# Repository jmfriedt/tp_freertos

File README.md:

# FreeRTOS on STM32 laboratory sessions

TP FreeRTOS on STM32F1VLDiscovery board or STM32F103 (update the LD script accordingly)

Assumes the Long Term Supported version of FreeRTOS as available at https://github.com/FreeRTOS/FreeRTOS-LTS 
(remember to ``git clone --recursive``), or the version found at https://www.freertos.org/a00104.html, is located at the same level than this set of examples: tune the Makefiles
accordingly for the header files and libraries to reach this directory. Former versions of FreeRTOSv9.0.0 or 
FreeRTOSv10.0.0 can be used as well: in that case tune the parameters of Makefile.v9 accordingly).

Compilation flags:
* ``-DSTM32F1`` or ``-DSTM32F4`` to select whether the board is fitted with and STM32F100/STM32F103 microcontroller
or with a STM32F407 (STM32F4Discovery)
* in case ``-DSTM32F1`` is selected, either select ``-DSTM32F10X_LD_VL`` for the STM32F100 ValueLine or the
``-DSTM32F10X_MD`` MediumDevice
* in case ``-DSTM32F10X_MD`` is selected, then add ``-Dsenseor`` for running on the hardware board (SENSeOR reader
fitted with the XE1203F radiomodem) without resetting the FTDI (keeping the GPIO connected to the FT232
reset pin as input). For running on Qemu, do not enable ``-Dsenseor``.
* the Texas Instruments Stellaris Cortex M4F core is supported and allows for simulating the execution
on the official qemu-system-arm emulator release: in that case, the linker script is ``stellaris.ld`` found in the ``ld`` directory.

Using ``libopencm3`` to provide system calls required by FreeRTOS running on the STM32 microcontroller (instead
of ST Microelectronics' libstm32) is described at http://www.jiggerjuice.info/electronics/projects/arm/freertos-stm32f103-port.html 
and was used in this set of demonstrations.

Tested with Andre Beckus' port of qemu to the stm32 (https://github.com/beckus/qemu_stm32): compile examples
for the STM32F103 (MD) device. Also tested with Renode (https://github.com/renode) emulating the STM32F103:

The Renode model has been updated to display GPIO/LED output state. Here also the very verbose gpioPortC status is displayed,
which can be removed by commenting (prefix with ``:``) the ``sysbus LogPeripheralAccess sysbus.gpioPortC`` line
in 1basic/stm32f103.resc

This set of laboratory sessions was developed independently but happens to closely match the topics of [Beginning STM32: Developing with FreeRTOS, libopencm3 and GCC](https://www.amazon.fr/Beginning-STM32-Developing-FreeRTOS-libopencm3/dp/1484236238) which might provide additional references to my own supporting material found at http://jmfriedt.free.fr under the Master1 section/embedded electronics/2nd semester. The
[github](https://github.com/ve3wwg/stm32f103c8t6) might provide complementary resources.

## References (in French)

* Q. Macé, J.-M Friedt, *FreeRTOS : application à la réalisation d'un analyseur de réseau 
numérique sur STM32*, <a href="http://jmfriedt.free.fr/lm_freertos.pdf">GNU/Linux Magazine France 
207</a> (Sept. 2017)
* J.-M Friedt, *Intercorrélation par transformée de Fourier rapide sur microcontroleur sous 
FreeRTOS, et les pointeurs de pointeurs*, <a href="http://jmfriedt.free.fr/lm_fft.pdf">Hackable 43 
</a>pp.4-- (Jul.-Aug. 2022)
* J.-M Friedt, *FreeRTOS dans 2,5 KB de RAM sur Atmega32U4*, <a href="http://jmfriedt.free.fr/hackable_atmega32u4.pdf">Hackable 48</a> (May/June 2023)

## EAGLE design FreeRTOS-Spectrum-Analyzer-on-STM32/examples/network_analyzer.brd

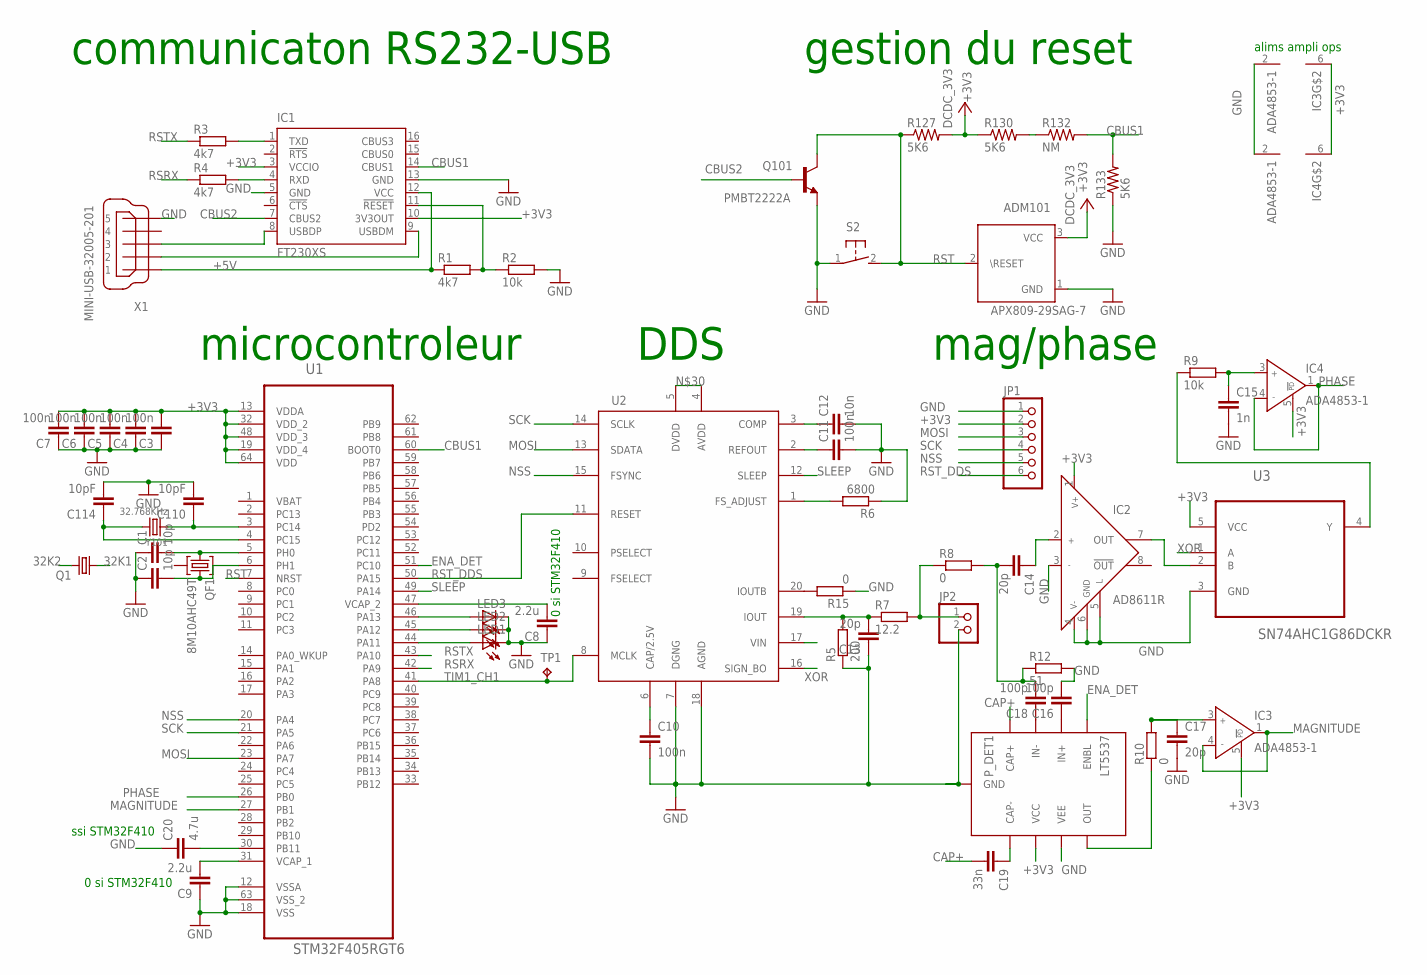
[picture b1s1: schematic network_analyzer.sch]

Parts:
ADM101: APX809-29SAG-7; CIS_SOT23_01
C1, C2: 10p; C0603
C3, C4, C5, C6, C7, C10, C11: 100n; C0603
C8, C9: 2.2u; C0402
C12: 10n; C0603
C13, C14, C17: 20p; C0603
C15: 1n; C0603
C16, C18: 100p; C0603
C19: 33n; C0603
C20: 4.7u; C0603
C110, C114: 10pF; C0402
IC1: FT230XS; SSOP16
IC2: AD8611R; SO8
IC3, IC4: ADA4853-1; SC70-6
JP1: PINHD-1X6; 1X06
JP2: PINHD-1X2; 1X02
LED1, LED2, LED3: LEDSML0603; SML0603
P_DET1: LT5537; 3X2MMDFN
Q1: CRYSTALTC26H; TC26H
Q101: PMBT2222A; Q-S_SOT23_01
QF1: 8M10AHC49T; HC49U
R1, R3, R4: 4k7; R0603
R2, R9: 10k; R0603
R5: 200; R0603
R6: 6800; R0603
R7: 12.2; 0207/10
R8, R10, R15: 0; R0603
R12: 51; R0603
R127, R130, R133: 5K6; R0402
R132: NM; R0402
S2: 31-XX; B3F-31XX
TP1: TPB1,27; B1,27
U1: STM32F405RGT6; QFP50P1200X1200X160-64N
U2: AD9834; TSSOP20
U3: SN74AHC1G86DCKR; SOT65P210X110-5N
X1: MINI-USB-32005-201; 32005-201
Y101: 32.768KHz; Y-S_3215_01

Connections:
32K1: C110.1, Q1.1, U1.3 (PC14), Y101.1
32K2: C114.1, Q1.2, U1.4 (PC15), Y101.2
+3V3: ADM101.3 (VCC), C3.2, C4.2, C5.2, C6.2, C7.2, IC1.3 (VCCIO), IC1.10 (3V3OUT), IC2.1 (V+), IC3.5 (!POWERDOWN), IC3.6 (V+), IC4.5 (!POWERDOWN), IC4.6 (V+), JP1.2, P_DET1.P$6 (VCC), R127.2, R130.1, U1.13 (VDDA), U1.19 (VDD_4), U1.32 (VDD_2), U1.48 (VDD_3), U1.64 (VDD), U3.5 (VCC)
+5V: IC1.12 (VCC), R1.1, X1.1
CAP+: C19.2, P_DET1.P$4 (CAP+)
CBUS1: IC1.14 (CBUS1), R132.2, R133.2, U1.60 (BOOT0)
CBUS2: IC1.7 (CBUS2), Q101.1 (B)
COMP: C12.1, U2.3 (COMP)
ENA_DET: P_DET1.P$1 (ENBL), U1.51 (PC10)
GND: ADM101.1 (GND), C1.1, C2.1, C3.1, C4.1, C5.1, C6.1, C7.1, C8.1, C9.1, C10.2, C11.2, C12.2, C13.1, C15.2, C16.2, C17.2, C20.1, C110.2, C114.2, IC1.5 (GND), IC1.13 (GND), IC2.3 (IN-), IC2.4 (V-), IC2.5 (L), IC2.6 (GND), IC3.2 (V-), IC4.2 (V-), JP1.1, JP2.2, LED1.C, LED2.C, LED3.C, P_DET1.P$7 (VEE), P_DET1.P$9 (GND), Q101.2 (E), R2.2, R5.1, R6.1, R12.2, R15.1, R133.1, S2.1, U1.12 (VSSA), U1.18 (VSS), U1.63 (VSS_2), U2.7 (DGNG), U2.17 (VIN), U2.18 (AGND), U3.3 (GND), X1.5
MAGNITUDE: IC3.1 (OUT), IC3.4 (IN-), U1.27 (PB1)
MOSI: JP1.3, U1.23 (PA7), U2.13 (SDATA)
unnamed: IC1.11 (!RESET), R1.2, R2.1
unnamed: IC1.8 (USBDP), X1.3
unnamed: IC1.9 (USBDM), X1.2
unnamed: C1.2, QF1.1, U1.5 (PH0)
unnamed: C2.2, QF1.3, U1.6 (PH1)
unnamed: IC1.4 (RXD), R4.2
unnamed: IC1.1 (TXD), R3.2
unnamed: C9.2, U1.31 (VCAP_1)
unnamed: C8.2, U1.47 (VCAP_2)
unnamed: C10.1, U2.6 (CAP/2.5V)
unnamed: C11.1, U2.2 (REFOUT)
unnamed: C13.2, R5.2, R7.1, U2.19 (IOUT)
unnamed: C15.1, IC4.3 (IN+), R9.2
unnamed: JP2.1, R7.2, R8.1
unnamed: R6.2, U2.1 (FS_ADJUST)
unnamed: P_DET1.P$8 (OUT), R10.1
unnamed: C14.1, IC2.2 (IN+)
unnamed: R9.1, U3.4 (Y)
unnamed: C19.1, P_DET1.P$5 (CAP-)
unnamed: C17.1, IC3.3 (IN+), R10.2
unnamed: R15.2, U2.20 (IOUTB)
unnamed: C18.1, P_DET1.P$3 (IN-)
unnamed: C16.1, P_DET1.P$2 (IN+)
unnamed: C14.2, C18.2, R8.2, R12.1
unnamed: LED1.A, U1.44 (PA11)
unnamed: LED2.A, U1.45 (PA12)
unnamed: LED3.A, U1.46 (PA13)
unnamed: C20.2, U1.30 (PB11)
unnamed: U2.4 (AVDD), U2.5 (DVDD)
unnamed: IC2.7 (OUT), U3.2 (B)
unnamed: R130.2, R132.1
NSS: JP1.5, U1.20 (PA4), U2.15 (FSYNC)
PHASE: IC4.1 (OUT), IC4.4 (IN-), U1.26 (PB0)
RSRX: R4.1, U1.42 (PA9)
RST: ADM101.2 (\RESET), Q101.3 (C), R127.1, S2.2 (S), U1.7 (NRST)
RSTX: R3.1, U1.43 (PA10)
RST_DDS: JP1.6, U1.50 (PA15), U2.11 (RESET)
SCK: JP1.4, U1.21 (PA5), U2.14 (SCLK)
SLEEP: U1.49 (PA14), U2.12 (SLEEP)
TIM1_CH1: TP1.TP, U1.41 (PA8), U2.8 (MCLK)
XOR: U2.16 (SIGN_BO), U3.1 (A)

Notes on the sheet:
alims ampli ops
0 si STM32F410
ssi STM32F410
gestion du reset
communicaton RS232-USB
microcontroleur
DDS
mag/phase

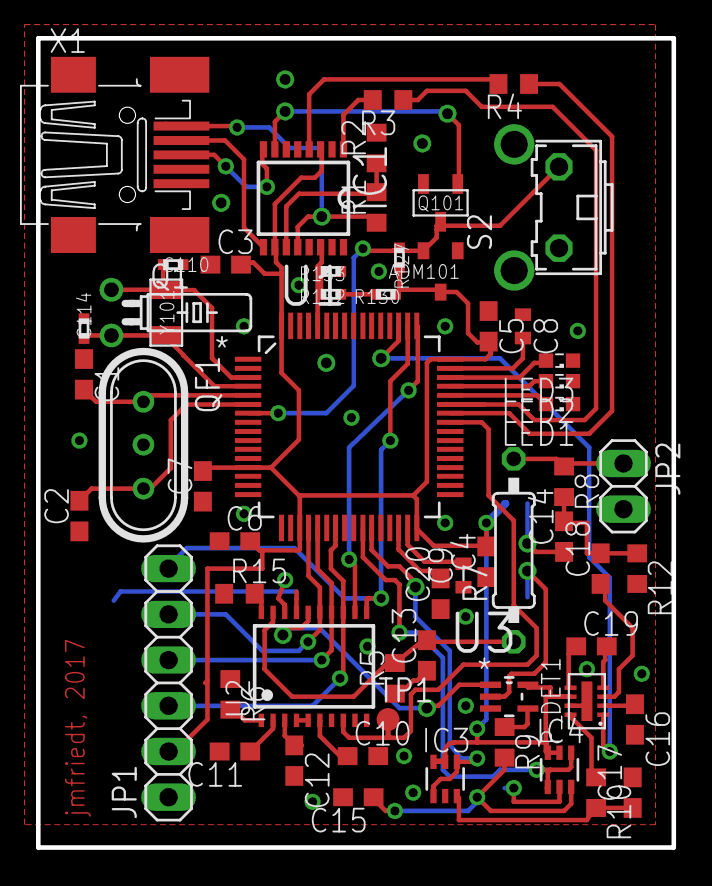
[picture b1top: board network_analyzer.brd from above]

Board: 2 copper layers, 35.3 x 45.0 mm, 59 parts (1 on the bottom side), 53 nets.

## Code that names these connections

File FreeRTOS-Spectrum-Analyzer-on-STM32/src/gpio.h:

//Port A
#define NSS GPIO4
#define SCK GPIO5
#define MISO GPIO6
#define MOSI GPIO7
#define TIM1_CH1 GPIO8
#define RSRX GPIO9
#define RSTX GPIO10
#define Led_Rouge GPIO11
#define Led_Jaune GPIO12
#define Led_Verte GPIO13
#define SLEEP GPIO14
#define RST_DDS GPIO15

//Port B
#define PHASE GPIO0
#define MAGNITUDE GPIO1

//Port C
#define ENA_DET GPIO10



void init_Gpio(void);
void delay(uint64_t delay);

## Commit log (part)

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2017-01-26 rm *.o *.bin *.elf
2017-01-26 libopencm3 compatibility with libstm32-based function prototypes
2017-02-24 cleanup prior to STM32F4 and libopencm3 support
2017-02-24 common files for libopencm3 support
2017-02-24 example without using FreeRTOS -- validates common/*
2017-02-24 example 1: basic FreeRTOS support
2017-02-24 corrected Makefile for F1
2017-02-24 example 1 tested on STM32F4-Discovery board
2017-02-24 example 2 for F1 (FreeRTOS v7 & v9) and F4 (v9)
2017-02-24 example 3 for F4/libopencm3
2017-02-25 cleanup
2017-02-25 examples 1-4 tested on STM32F103
2017-02-28 STM32F100VL option
2017-02-28 for STM32F100VL
2017-02-28 example 5
2017-03-09 philosophes
2017-05-12 Network analyzer project
2017-05-12 circuit
2017-05-12 warning cleanup
2017-05-14 retire redonance d'ordonnancement
2017-06-20 example of architecture selection by flags
2017-06-21 directory name
2018-01-24 LD script position correction
2018-01-24 common/usart
2018-01-24 Makefile.f1
2018-01-24 3mutex example
2018-01-24 -g option
2018-02-02 f103 v.s f1(00): MD v.s LD
2018-02-05 init F4
2018-02-05 STM32F4Disco -> netwk analyzer
2018-02-09 output directories:
2018-02-09 Makefile for F4 with correct ld path
2018-02-10 remove unnecessary library references in F4 Makefile(s)
2018-02-11 FreeRTOS v9 -> v10
2018-02-11 remove tmp dir
2018-08-27 separate libopencm3 from SAT when using Debian arm-none-eabi-* & FreeRTOS v9 -> v10
2018-09-02 new libopencm3 dropped timer_reset
2018-09-02 F3 Makefile
2018-09-02 F4 Makefile
2018-09-02 reset timer
2018-09-02 reset definition
2019-03-08 190308
2019-03-09 Only handle LEDs *after* init clocks
2019-03-15 include
2019-03-15 Makefile ADC
2019-03-15 Makefile
2019-03-15 ADC main
2019-10-27 stdio + common header
2019-10-27 new clock setup
2020-01-20 add stellaris support for official arm-qemu simulation
2020-08-29 Makefile update
2020-08-29 linker script for F103
2020-08-29 avoid reset of FTDI on SENSeOR board
2021-01-16 Makefile: FreeRTOS LTS and libopencm3 in /home/jmfriedt
2021-04-01 remove sat
2021-06-03 README: update to LTS FreeRTOS
2021-07-10 Renode simulation of FreeRTOS on STM32F103
2021-07-10 renode picture
2021-07-10 Renode simulation with GPIO/LED display
2021-08-23 STM32F4 custom clock initialization to reflect latest (Aug. 2021) libopencm3 API
2022-01-20 Makefile for 202112 version of FreeRTOS
2022-01-21 path to FreeRTOS
2022-01-22 reduce RAM requirement to match qemu configuration
2022-01-27 PATH to qemu and FreeRTOS
2022-01-28 README flags
2022-01-28 update libopencm3 clock initialization
2022-03-13 initial commit: FFT in FreeRTOS for xcorr calculation
2022-03-17 remove incorrect submodule
2022-03-17 remove erroneous submodule entry
2022-03-17 add CMSIS submodule
2022-03-17 8_xcorr_fft/src/main.c
2022-03-18 pucture
2022-03-18 README
2022-03-18 picture
2022-03-18 clean Makefile from unnecessary CMSIS dependencies
2022-03-18 url of FreeRTOS LTS source
2022-03-18 README including stellaris support
2022-03-18 datasets
2022-03-18 solution to the exam
2022-03-18 comment on chart
2022-03-19 add KISSFFT
2022-03-25 functional KISSFFT demonstration up to 128 FFT
2022-03-28 CMSIS to STM32 and check static array allocation
2022-03-28 FFT example README
2023-01-13 update Makefile
2023-01-13 Makefile clean method
2023-01-13 Makefile senseor
2023-01-27 FreeRTOS location as variable in Makefile
2023-01-29 UART init first to avoid clock warning
2023-03-17 AVR support
2023-03-18 AVR generic functions
2023-03-18 Atmega32U4 port
2023-03-21 Add stack hook + tune RAM size to match hardware
2023-04-01 Atmega32U4 support location
2023-10-08 implement ADC in common
2023-10-08 ADC stub for PC
2024-01-18 typo README
2025-01-24 update Makefile for LTS
2025-01-24 remove warnings for ISR
2025-01-31 init UART (and clocks) BEFORE leds
2025-01-31 temperature
2025-01-31 update temperature
2025-01-31 update temperature Makefile
2025-01-31 update temperature linker script (RAM size)
2025-02-03 update solutions
2025-02-06 update temperature example for STM32F100VL-Discovery
2025-05-23 add some RISC-V support
2026-01-23 update all Makefiles to use heap4
2026-01-23 add FreeRTOSConfig.h as Makefile dependency
2026-01-23 remove asm startup file
2026-01-23 add Makefile
2026-01-23 conditional display
2026-01-27 STM32VLdiscovery makefile compatible with official qemu
2026-01-27 update Renode peripheral name + Mutex demonstration on CM4 using (proper qemu timing)
2026-01-28 cleanup 0 and 1
2026-01-28 cleanup 2 and 3
2026-01-29 add README with qemu procedure
2026-01-29 add renode
2026-03-18 initial Red Pitaya support
2026-03-19 update Red Pitaya baremetal submodule
2026-05-07 redpitaya baremetal
2026-06-26 add Red Pitaya support framework... not functional
